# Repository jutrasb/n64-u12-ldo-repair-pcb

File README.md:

# Nintendo 64 U12 LDO Repair PCB
KiCad Project for Nintendo 64 U12 LDO Repair PCB

# Background

I came across a Nintendo 64 NUS-CPU-05 motherboard with a seemingly dead Sharp PQ7VZ5 linear regulator at U12. This component is obsolete and has an awkward pinout which prevents simple replacement.

This PCB is an attempt to substitute the Sharp PQ7VZ5 linear regulator using a compatible footprint connected to a Texas Instruments TLV78525PDBVR. This linear regulator has a fixed output of 2.5V and it's extremely cheap and common, making it a suitable replacement.

Theoretically, this PCB would work for any Sharp PQ7VZ5 linear regulator replacement, but please note that other changes may be required when using other voltages.

# BOM

| Component | Manufacturer | Description | Quantity | DigiKey Part # |
| -- | -- | -- | -- | -- |
| U1 | Texas Instruments | Linear Voltage Regulator IC Positive Fixed 1 Output 500mA SOT-23-5 | 1 | 296-TLV78525PDBVRCT-ND |
| C1, C2 | Murata Electronics | 1 µF ±20% 16V Ceramic Capacitor X5R 0402 (1005 Metric) | 2 | 490-14599-1-ND
| R1 | Stackpole Electronics Inc | 100 kOhms ±5% 0.063W, 1/16W Chip Resistor 0402 (1005 Metric) Automotive AEC-Q200 Thick Film | 1 | RMCF0402JT100KCT-ND

# PCB Fabrication Notes

0.6mm thickness or flexible PCB recommended.

# Render

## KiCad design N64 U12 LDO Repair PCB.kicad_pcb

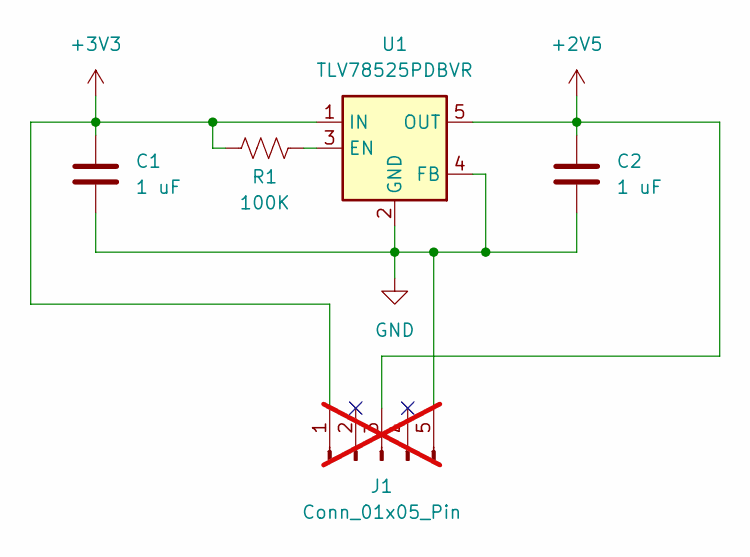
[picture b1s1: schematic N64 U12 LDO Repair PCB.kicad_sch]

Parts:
C1, C2: 1 uF; C_0402_1005Metric_Pad0.74x0.62mm_HandSolder
J1: Conn_01x05_Pin; CustomAdapter_SharpPQ7VZ5; not fitted
R1: 100K; R_0402_1005Metric_Pad0.72x0.64mm_HandSolder
U1: TLV78525PDBVR; SOT-23-5

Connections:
+2V5: C2.1, J1.3, U1.5 (OUT)
+3V3: C1.1, J1.1, R1.1, U1.1 (IN)
GND: C1.2, C2.2, J1.5, U1.2 (GND), U1.4 (FB)
unnamed: R1.2, U1.3 (EN)

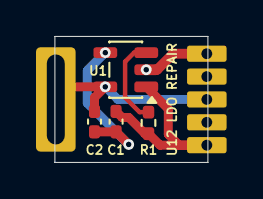
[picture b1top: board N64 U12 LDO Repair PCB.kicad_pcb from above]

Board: 2 copper layers, 8.5 x 7.0 mm, 5 parts (0 on the bottom side), 4 nets.
